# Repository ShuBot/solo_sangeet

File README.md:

# solo_sangeet
ESP32 based music player.

### useful links:
- get color hex codes: https://rgbcolorpicker.com/
- HEX converter: https://www.rapidtables.com/convert/number/decimal-to-hex.html
- LVGL Library: https://github.com/lvgl/lvgl (Add to "solo_sangeet/components/lvgl")
- LVGL Live Preview VS Code extension: https://github.com/themastercoder007/lvgl-live-preview
- Ref for display driver: [ESP-IDF]/examples/peripherals/lcd/spi_lcd_touch/README.md

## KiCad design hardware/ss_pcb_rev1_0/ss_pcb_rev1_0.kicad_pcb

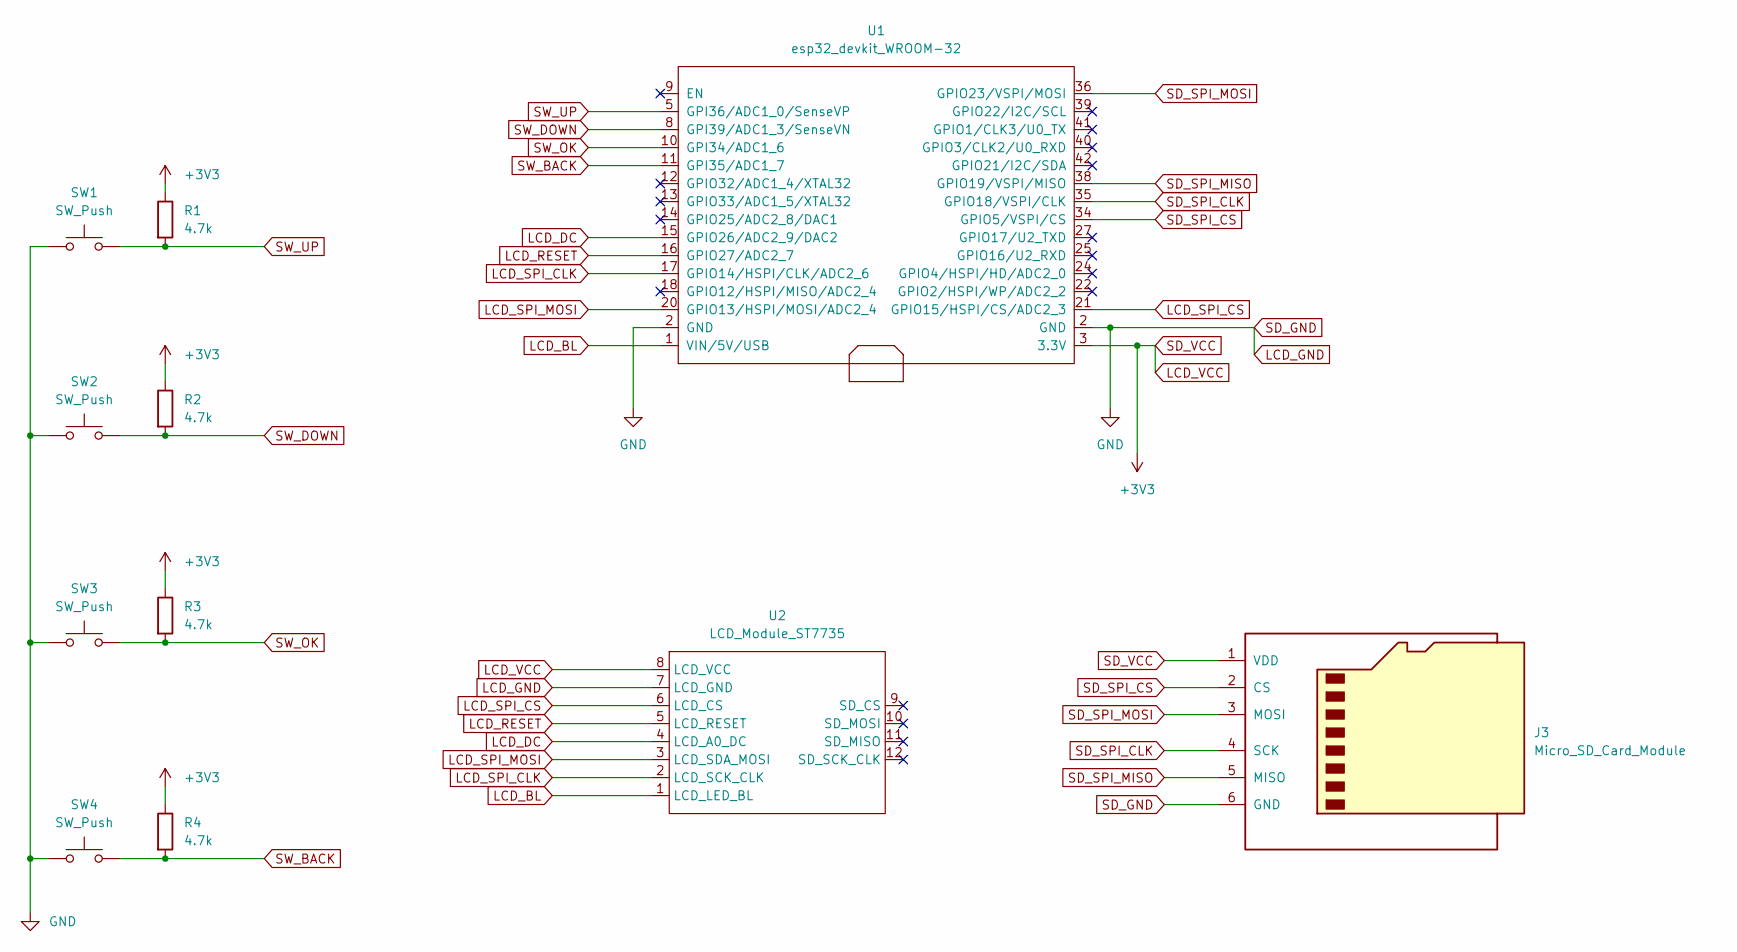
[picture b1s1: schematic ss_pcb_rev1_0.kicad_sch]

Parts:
J3: Micro_SD_Card_Module; MicroSD Card Reader
R1, R2, R3, R4: 4.7k; R_Axial_DIN0204_L3.6mm_D1.6mm_P7.62mm_Horizontal
SW1, SW2, SW3, SW4: SW_Push; SW_PUSH_6mm
U1: esp32_devkit_WROOM-32; ESP32_DevKit_V1_DOIT_Module
U2: LCD_Module_ST7735

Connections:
LCD_BL: U1.1 (VIN/5V/USB), U2.1 (LCD_LED_BL)
LCD_DC: U1.15 (GPIO26/ADC2_9/DAC2), U2.4 (LCD_A0_DC)
LCD_GND: J3.6 (GND), SW1.1, SW2.1, SW3.1, SW4.1, U1.2 (GND), U2.7 (LCD_GND)
LCD_RESET: U1.16 (GPIO27/ADC2_7), U2.5 (LCD_RESET)
LCD_SPI_CLK: U1.17 (GPIO14/HSPI/CLK/ADC2_6), U2.2 (LCD_SCK_CLK)
LCD_SPI_CS: U1.21 (GPIO15/HSPI/CS/ADC2_3), U2.6 (LCD_CS)
LCD_SPI_MOSI: U1.20 (GPIO13/HSPI/MOSI/ADC2_4), U2.3 (LCD_SDA_MOSI)
LCD_VCC: J3.1 (VDD), R1.1, R2.1, R3.1, R4.1, U1.3 (3.3V), U2.8 (LCD_VCC)
SD_SPI_CLK: J3.4 (SCK), U1.35 (GPIO18/VSPI/CLK)
SD_SPI_CS: J3.2 (CS), U1.34 (GPIO5/VSPI/CS)
SD_SPI_MISO: J3.5 (MISO), U1.38 (GPIO19/VSPI/MISO)
SD_SPI_MOSI: J3.3 (MOSI), U1.36 (GPIO23/VSPI/MOSI)
SW_BACK: R4.2, SW4.2, U1.11 (GPI35/ADC1_7)
SW_DOWN: R2.2, SW2.2, U1.8 (GPI39/ADC1_3/SenseVN)
SW_OK: R3.2, SW3.2, U1.10 (GPI34/ADC1_6)
SW_UP: R1.2, SW1.2, U1.5 (GPI36/ADC1_0/SenseVP)

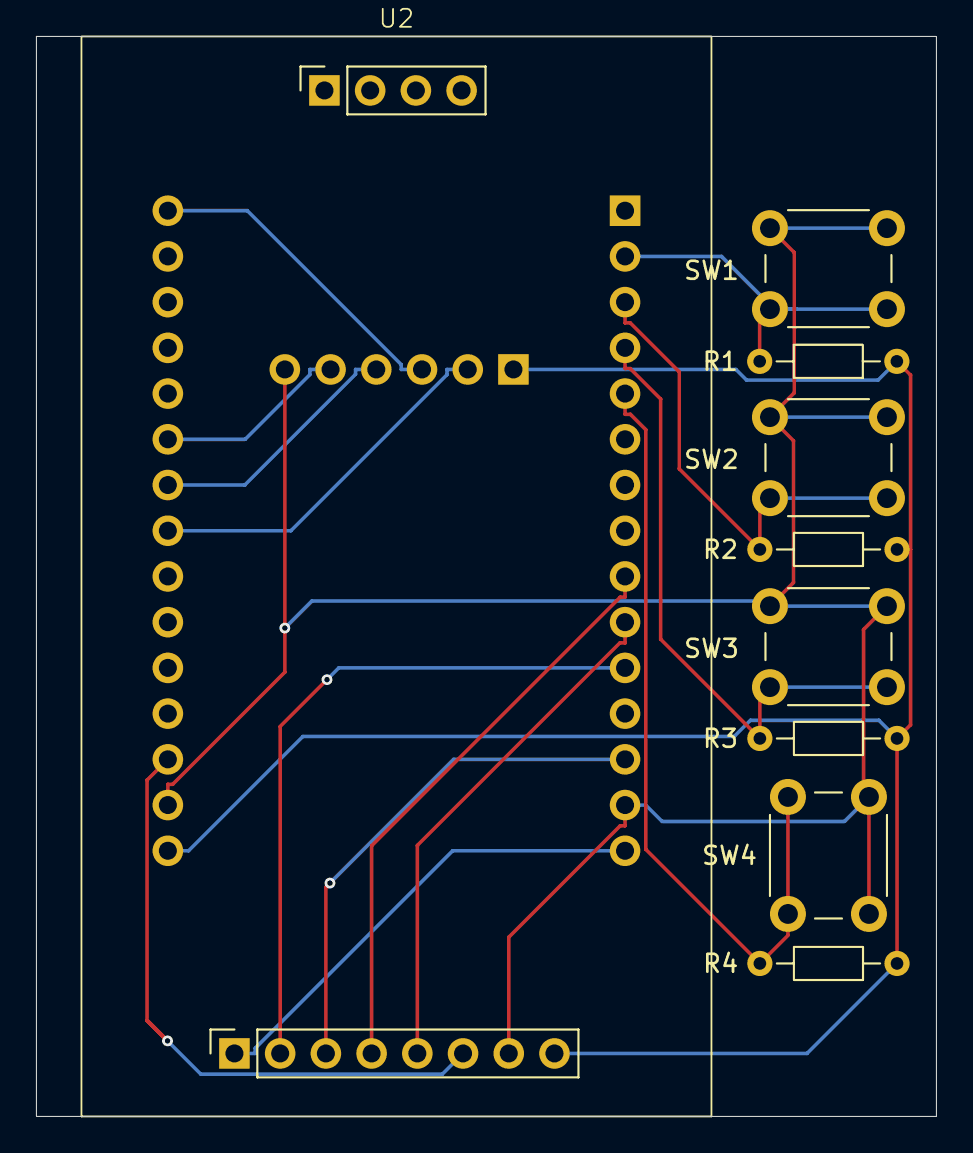
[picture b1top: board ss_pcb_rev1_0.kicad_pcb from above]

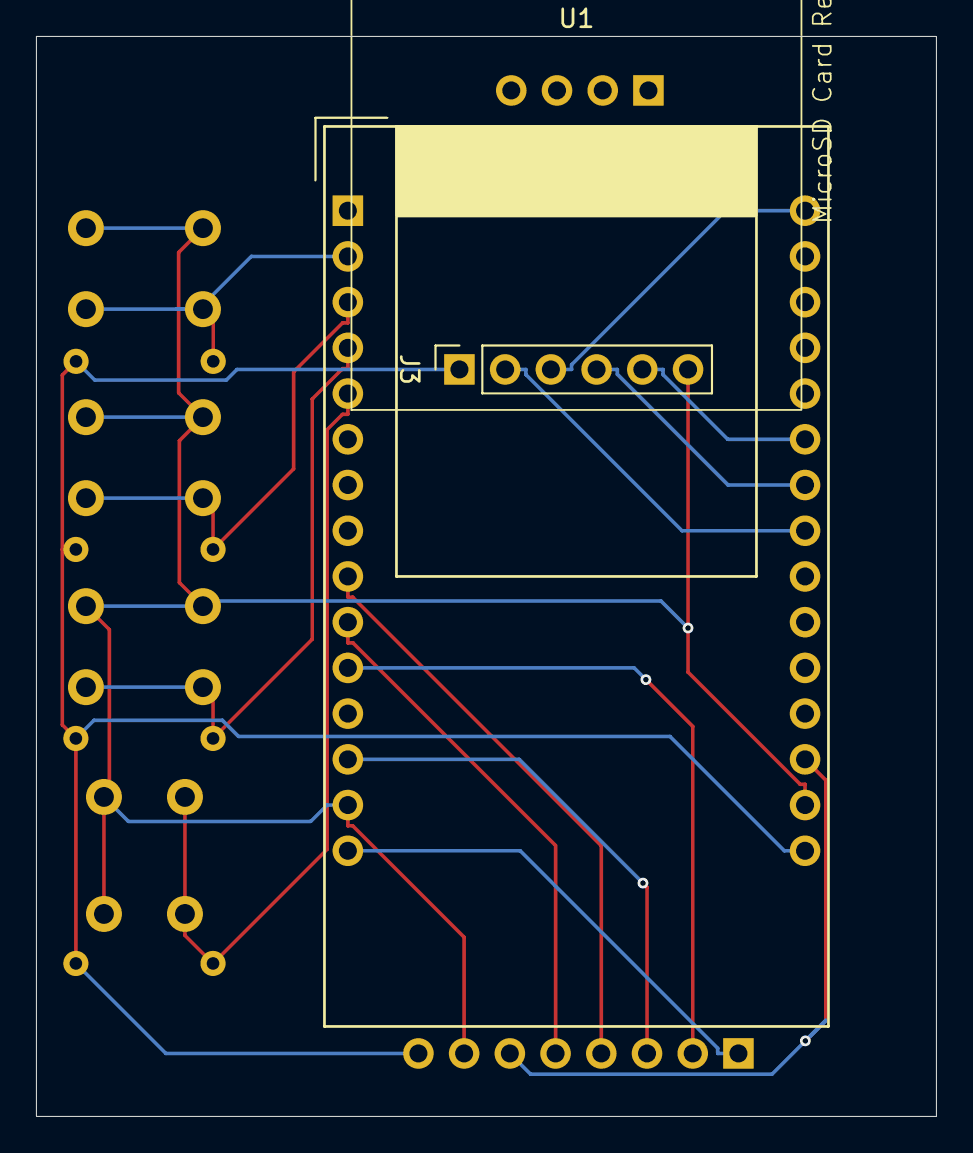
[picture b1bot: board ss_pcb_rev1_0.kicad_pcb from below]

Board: 2 copper layers, 50.0 x 60.0 mm, 11 parts (2 on the bottom side), 16 nets.

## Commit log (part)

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2025-04-08 first commint, started writing display drivers
2025-08-17 Adds LVGL library, and test code.
2025-08-17 removing some commented code.
2025-08-17 updates readme, lvgl link
2025-08-20 adds screen orientation command
2025-08-27 Updates st7735_driver names, macros. Adds ili9488_driver as esp component.
2025-09-07 Adds SPI buffer transfer for faster display updates.
2025-09-07 updates spi buffer flush cb with right color settings
2025-09-15 Upgrades LVGL library in the project to version: 9.3.0, and adds image examples.
2025-09-25 Adds rev1_0 hardware design files.
2025-12-29 Adds ILI9341 lcd driver, and removes ILI9488 driver.
2025-12-29 Updates main code for ili9341 display.
2025-12-29 Updates ILI9341 drivers, and lvgl flush callback. All colors set right.
2025-12-29 Updates DMA spi for fill screen and fill rect APIs.
2025-12-29 Adds lvgl_flush with spi dma. Adds custom lv_conf.h for color swap.
2025-12-29 Adds touch driver for lvgl input processing.
2025-12-30 Updates touch sensor calibration, wrt elecro display module.
2025-12-30 Adds BT Audio library from A2DP_source example code.
2025-12-30 Adds SD Card read/write library, init.
2025-12-31 Adds audio_player library to manage and play audio files, via BT. All audio play related tasks & APIs will be here.
2026-01-01 Updates audio_player task with state machine to control play and stop. Stable.
2026-01-13 Updates lv_config.h, UI and removes test UI images.
2026-01-18 Adds UI design tools. VS Code Ext: LVGL Live Preview.
2026-01-18 Updates UI with lv_menu, multiple pages and navigation bar.
2026-01-18 Adds UI control for LCD Backlight brightness.
2026-01-23 Adds Status Bar on top of screen, with Battery WiFi and BT.
2026-01-23 Adds Feature: BT scanning & connect via touch UI.
2026-01-29 Adds themes structure for the UI.
2026-01-29 Updates options page styles in the UI.
2026-01-29 Adds themes structure for the lvgl UI.
2026-03-23 updates rev_0 hw design files.
2026-05-31 removes wifi from menu, for now
2026-05-31 Updates ili9341_driver with ili9341_flush_spi_dma_async for faster screen updates.
2026-05-31 Updates main with test_lvgl option to test various LVGL features. Testing Lottie Player now.
